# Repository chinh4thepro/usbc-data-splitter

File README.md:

This is a board that splits up two usb-c connectors and combines it into one, one for power and one for data. This is useful in situations where you need usb PD but the device doesn't support it or unable to output it.

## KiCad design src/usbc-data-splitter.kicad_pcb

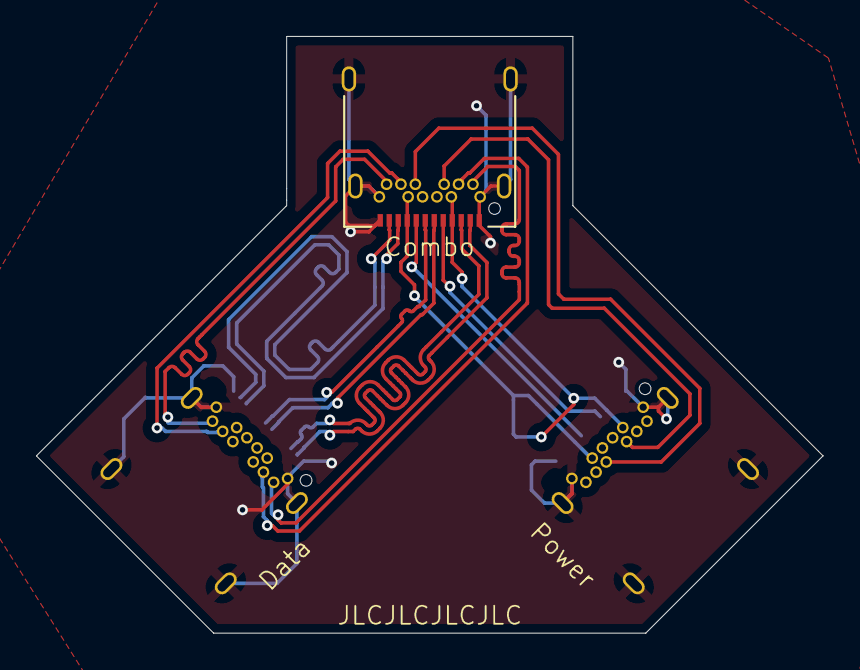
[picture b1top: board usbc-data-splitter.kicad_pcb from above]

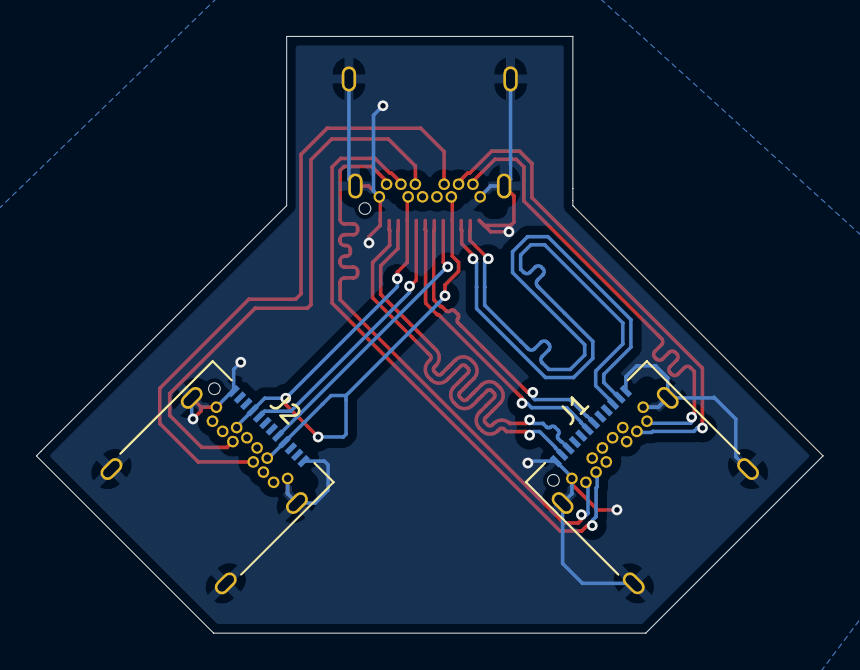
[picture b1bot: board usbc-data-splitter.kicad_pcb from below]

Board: 2 copper layers, 43.7 x 33.2 mm, 3 parts (2 on the bottom side), 16 nets.

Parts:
J1: Data; USB_C_Receptacle_Amphenol_12401548E4-2A
J2: Power; USB_C_Receptacle_Amphenol_12401548E4-2A
P1: Combined; USB_C_Receptacle_Amphenol_12401548E4-2A

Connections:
CC: J2.A5 (CC1), P1.A5 (CC)
D_N: J1.A7 (D-), P1.A7 (D-)
D_P: J1.A6 (D+), P1.A6 (D+)
GND: J1.A1 (GND), J1.A12 (GND), J1.B1 (GND), J1.B12 (GND), J1.S1 (SHIELD), J2.A1 (GND), J2.A12 (GND), J2.B1 (GND), J2.B12 (GND), J2.S1 (SHIELD), P1.A1 (GND), P1.A12 (GND), P1.B1 (GND), P1.B12 (GND), P1.S1 (SHIELD)
RX1_N: J1.B10 (RX1-), P1.B10 (RX1-)
RX1_P: J1.B11 (RX1+), P1.B11 (RX1+)
RX2_N: J1.A10 (RX2-), P1.A10 (RX2-)
RX2_P: J1.A11 (RX2+), P1.A11 (RX2+)
SBU1: J2.A8 (SBU1), P1.A8 (SBU1)
SBU2: J2.B8 (SBU2), P1.B8 (SBU2)
TX1_N: J1.A3 (TX1-), P1.A3 (TX1-)
TX1_P: J1.A2 (TX1+), P1.A2 (TX1+)
TX2_N: J1.B3 (TX2-), P1.B3 (TX2-)
TX2_P: J1.B2 (TX2+), P1.B2 (TX2+)
VBUS: J2.A4 (VBUS), J2.A9 (VBUS), J2.B4 (VBUS), J2.B9 (VBUS), P1.A4 (VBUS), P1.A9 (VBUS), P1.B4 (VBUS), P1.B9 (VBUS)
VCON: J2.B5 (CC2), P1.B5 (VCONN)

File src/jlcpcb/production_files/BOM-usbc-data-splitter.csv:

Comment,Designator,Footprint,LCSC,Quantity
Data,"J1,J2,P1",USB_C_Receptacle_Amphenol_12401548E4-2A,C3197858,3

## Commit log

2025-08-22 Fix journal and add a gitignore.
2025-08-24 finished.
2025-08-24 what
2025-08-24 fix image
2025-08-24 screw holes
2025-08-24 differential pair tuning
2025-08-24 remove KiCAD directory as it is the src directory now
2025-08-24 Update rendered pcb pic
